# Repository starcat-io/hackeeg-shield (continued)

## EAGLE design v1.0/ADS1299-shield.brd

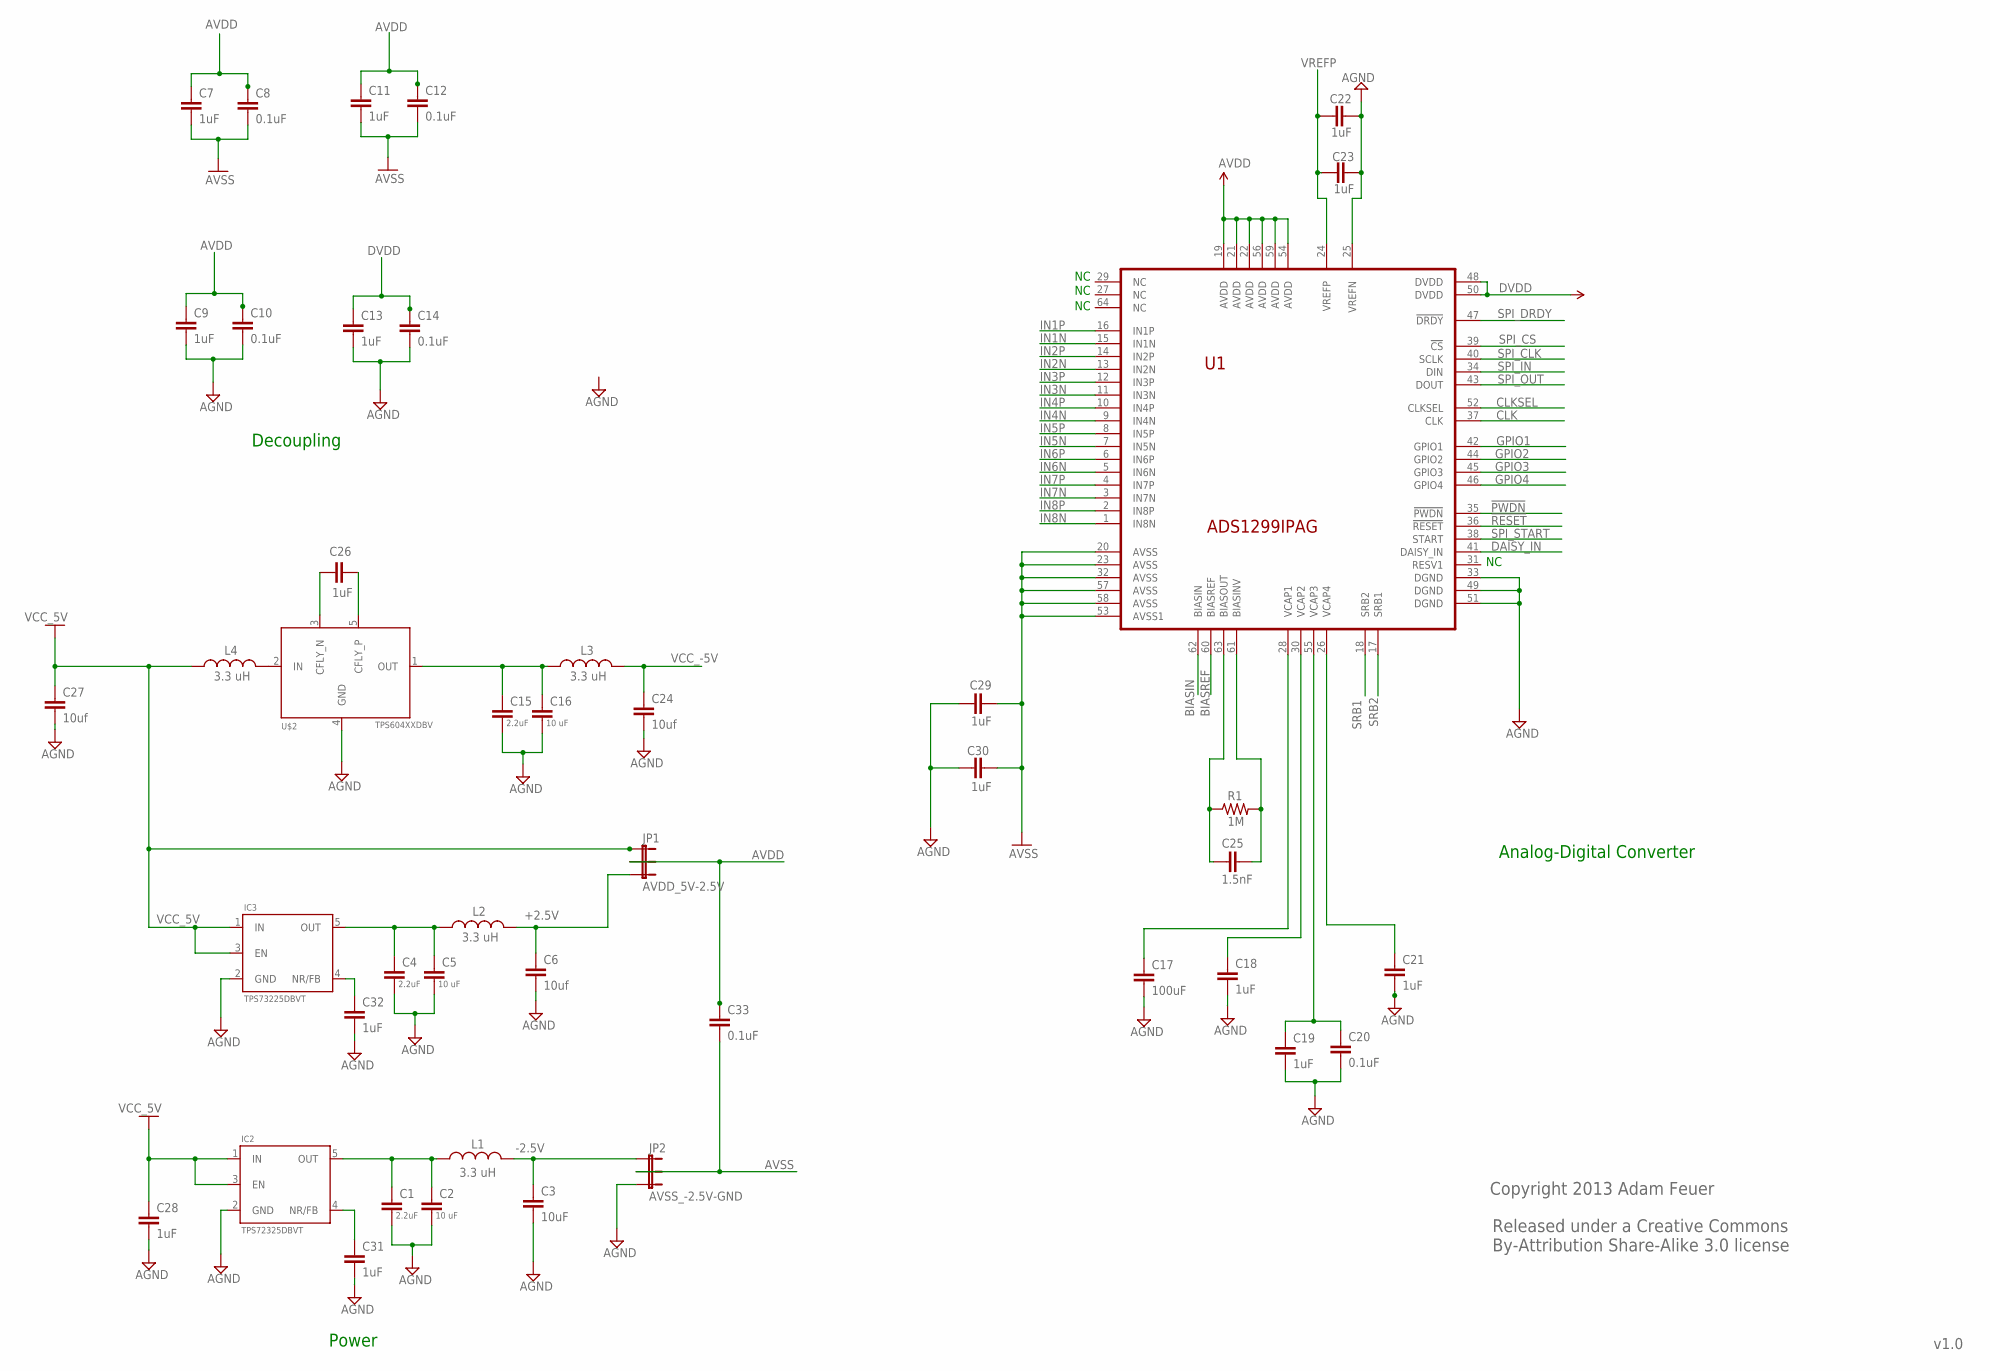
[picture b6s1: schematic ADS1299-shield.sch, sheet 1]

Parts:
C1, C4, C15: 2.2uF; 0603-CAP
C2, C5, C16: 10 uF; 0603-CAP
C3: 10uF; 0603-CAP
C6, C24, C27: 10uf; 0603-CAP
C7, C9, C11, C13, C18, C19, C21, C22, C23, C26, C28, C29, C30, C31, C32: 1uF; 0603-CAP
C8, C10, C12, C14, C20, C33: 0.1uF; 0603-CAP
C17: 100uF; 0603-CAP
C25: 1.5nF; 0603-CAP
IC2: TPS72325DBVT; SOT23-5
IC3: TPS73225DBVT; SOT23-5
JP1: AVDD_5V-2.5V; 1X03
JP2: AVSS_-2.5V-GND; 1X03
L1, L2, L3, L4: 3.3 uH; 0603
R1: 1M; 0603-RES
U1: ADS1299IPAG; TQFP64
U$2: TPS604XXDBV; SOT23-5

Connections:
!PWDN: U1.35 (!PWDN)
!RESET: U1.36 (!RESET)
+2.5V: C6.1, JP1.3, L2.2
-2.5V: C3.1, JP2.1, L1.2
AGND: C1.2, C2.2, C3.2, C4.2, C5.2, C6.2, C9.2, C10.2, C13.2, C14.2, C15.2, C16.2, C17.2, C18.2, C19.2, C20.2, C21.2, C22.2, C23.2, C24.2, C27.2, C28.2, C29.1, C30.1, C31.2, C32.2, IC2.2 (GND), IC3.2 (GND), JP2.3, U1.25 (VREFN), U1.33 (DGND), U1.49 (DGND), U1.51 (DGND), U$2.4 (GND); also elsewhere on the board
AVDD: C7.1, C8.1, C9.1, C10.1, C11.1, C12.1, C33.1, JP1.2, U1.19 (AVDD), U1.21 (AVDD), U1.22 (AVDD), U1.54 (AVDD), U1.56 (AVDD), U1.59 (AVDD)
AVSS: C11.2, C12.2, C29.2, C30.2, C33.2, JP2.2, U1.20 (AVSS), U1.23 (AVSS), U1.32 (AVSS), U1.53 (AVSS1), U1.57 (AVSS), U1.58 (AVSS)
BIASIN: U1.62 (BIASIN)
BIASINV: C25.2, R1.2, U1.61 (BIASINV)
BIASOUT: C25.1, R1.1, U1.63 (BIASOUT)
BIASREF: U1.60 (BIASREF)
CLK: U1.37 (CLK)
CLKSEL: U1.52 (CLKSEL)
DAISY_IN: U1.41 (DAISY_IN)
DVDD: C13.1, C14.1, U1.48 (DVDD), U1.50 (DVDD)
GND: C7.2, C8.2
GPIO1: U1.42 (GPIO1)
GPIO2: U1.44 (GPIO2)
GPIO3: U1.45 (GPIO3)
GPIO4: U1.46 (GPIO4)
IN1N: U1.15 (IN1N); also elsewhere on the board
IN1P: U1.16 (IN1P); also elsewhere on the board
IN2N: U1.13 (IN2N); also elsewhere on the board
IN2P: U1.14 (IN2P)
IN3N: U1.11 (IN3N)
IN3P: U1.12 (IN3P); also elsewhere on the board
IN4N: U1.9 (IN4N); also elsewhere on the board
IN4P: U1.10 (IN4P); also elsewhere on the board
IN5N: U1.7 (IN5N); also elsewhere on the board
IN5P: U1.8 (IN5P); also elsewhere on the board
IN6N: U1.5 (IN6N); also elsewhere on the board
IN6P: U1.6 (IN6P); also elsewhere on the board
IN7N: U1.3 (IN7N); also elsewhere on the board
IN7P: U1.4 (IN7P); also elsewhere on the board
IN8N: U1.1 (IN8N); also elsewhere on the board
IN8P: U1.2 (IN8P); also elsewhere on the board
unnamed: C4.1, C5.1, IC3.5 (OUT), L2.1
unnamed: C1.1, C2.1, IC2.5 (OUT), L1.1
unnamed: C17.1, U1.28 (VCAP1)
unnamed: C18.1, U1.30 (VCAP2)
unnamed: C19.1, C20.1, U1.55 (VCAP3)
unnamed: C15.1, C16.1, L3.1, U$2.1 (OUT)
unnamed: C21.1, U1.26 (VCAP4)
unnamed: C26.2, U$2.5 (CFLY_P)
unnamed: C26.1, U$2.3 (CFLY_N)
unnamed: C32.1, IC3.4 (NR/FB)
unnamed: L4.2, U$2.2 (IN)
unnamed: C31.1, IC2.4 (NR/FB)
SPI_CLK: U1.40 (SCLK)
SPI_CS: U1.39 (!CS)
SPI_DRDY: U1.47 (!DRDY)
SPI_IN: U1.34 (DIN)
SPI_OUT: U1.43 (DOUT)
SPI_START: U1.38 (START)
SRB1: U1.18 (SRB2)
SRB2: U1.17 (SRB1)
VCC_5V: C27.1, IC3.1 (IN), IC3.3 (EN), JP1.1, L4.1
VCC_-5V: C24.1, C28.1, IC2.1 (IN), IC2.3 (EN), L3.2
VREFP: C22.1, C23.1, U1.24 (VREFP)

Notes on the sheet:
Released under a Creative Commons By-Attribution Share-Alike 3.0 license
Copyright 2013 Adam Feuer
v1.0
Decoupling
Power
Analog-Digital Converter

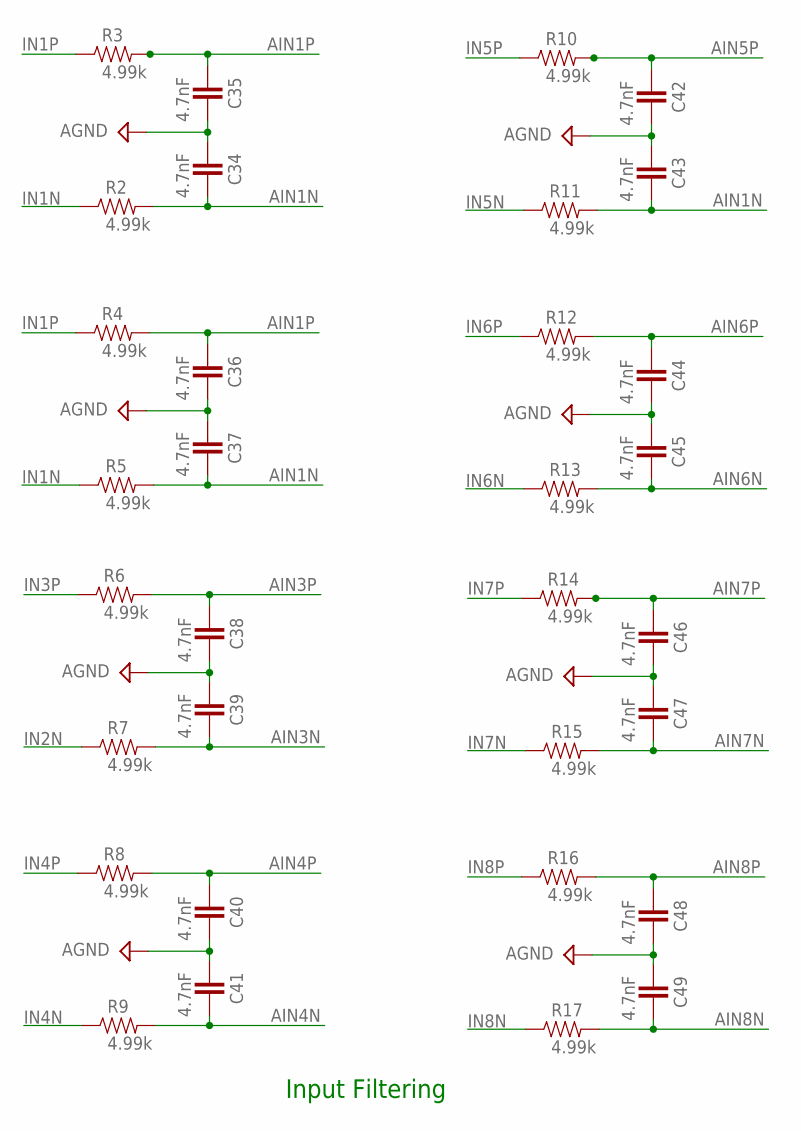
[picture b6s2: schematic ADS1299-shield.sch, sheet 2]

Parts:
C34, C35, C36, C37, C38, C39, C40, C41, C42, C43, C44, C45, C46, C47, C48, C49: 4.7nF; 0603-CAP
R2, R3, R4, R5, R6, R7, R8, R9, R10, R11, R12, R13, R14, R15, R16, R17: 4.99k; 0603-RES

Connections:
AGND: C34.1, C35.2, C36.2, C37.1, C38.2, C39.1, C40.2, C41.1, C42.2, C43.1, C44.2, C45.1, C46.2, C47.1, C48.2, C49.1; also elsewhere on the board
AIN1N: C34.2, C37.2, C43.2, R2.2, R5.2, R11.2
AIN1P: C35.1, C36.1, R3.2, R4.2
AIN3N: C39.2, R7.2
AIN3P: C38.1, R6.2
AIN4N: C41.2, R9.2
AIN4P: C40.1, R8.2
AIN5P: C42.1, R10.2
AIN6N: C45.2, R13.2
AIN6P: C44.1, R12.2
AIN7N: C47.2, R15.2
AIN7P: C46.1, R14.2
AIN8N: C49.2, R17.2
AIN8P: C48.1, R16.2
IN1N: R2.1, R5.1; also elsewhere on the board
IN1P: R3.1, R4.1; also elsewhere on the board
IN2N: R7.1; also elsewhere on the board
IN3P: R6.1; also elsewhere on the board
IN4N: R9.1; also elsewhere on the board
IN4P: R8.1; also elsewhere on the board
IN5N: R11.1; also elsewhere on the board
IN5P: R10.1; also elsewhere on the board
IN6N: R13.1; also elsewhere on the board
IN6P: R12.1; also elsewhere on the board
IN7N: R15.1; also elsewhere on the board
IN7P: R14.1; also elsewhere on the board
IN8N: R17.1; also elsewhere on the board
IN8P: R16.1; also elsewhere on the board

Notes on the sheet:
Input Filtering

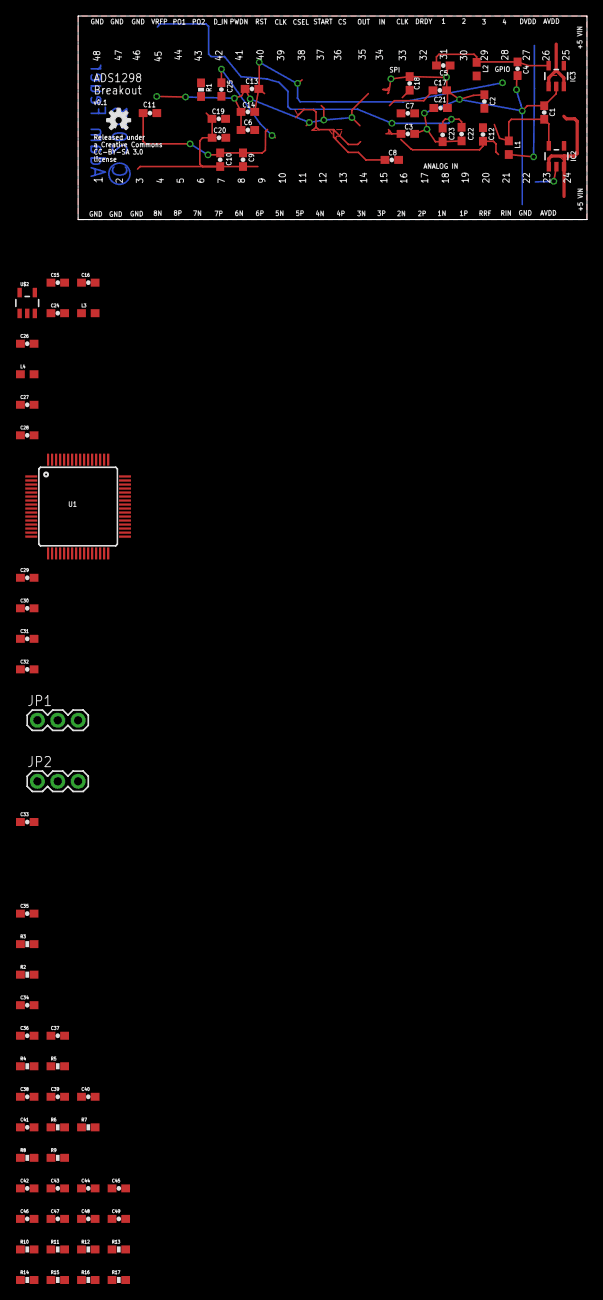
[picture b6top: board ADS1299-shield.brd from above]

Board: 2 copper layers, 63.5 x 25.4 mm, 77 parts (0 on the bottom side), 51 nets.

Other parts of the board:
U$1: OSHW-LOGO-S

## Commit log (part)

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2013-11-05 initial addition, based on ADS1298-breakout
2013-11-06 initial addition of ads129x.lbr - has ADS1298 and ADS1299 chips
2013-11-06 added TI TPS604xx.lbr
2013-11-06 renamed ADS129x.lbr to capitalize ADS
2013-11-06 library-cleanup - positioned symbol corrrectly
2013-11-06 initial addition of OPA376 library
2013-11-06 schematic work - power supplies and decoupling done; updated ADS1299 library symbol to better organize pinouts; minor updates to power supply libraries
2013-11-07 input filtering section done
2013-11-08 configuration jumpers added but not done; EEPROM in and finished; level shifters finished
2013-11-09 configuration jumpers almost complete - board address in, and all configurable digital signals in
2013-11-09 added 2x15 header to header library; used it for electrode connector, which is finished
2013-11-09 removed unneeded burr-brown library
2013-11-10 corrected mixed up N and P pins in OPA375 library; some cleanup
2013-11-11 board outline in, copied from Arduino Due reference design; holes in; connectors in both schematic and board, but not connected in schematic
2013-11-11 all components on board, but not arranged well; connectors not hooked up
2013-11-11 added wires for labeling SPI and XIO connectors
2013-11-11 wires and labels added for SPI and XIO connectors
2013-11-12 all necessary signals routed to shield connectors; schematic passes ERC
2013-11-13 added test points for power; added fiducials; partially grouped AIN block passives, EEPROM resistors, and level shifter decoupling caps
2013-11-13 arranged components by function - AIN filters, ADC and decoupling, power, SRB, Bias, level shifters, EEPROM
2013-11-14 fixed errors in AIN block; some airwires; level shifter output enable is now connected and held high
2013-11-15 changed sync connector to jst 3-pin to support start and clock signals; moved components to place jst connector at board left edge; made ground and power polygons
2013-11-15 new component arrangement - AIN block neat; configuration blocks moved to make more space for routing
2013-11-16 updated 2X10 and 2X12 headers to use smaller pads that can route 2 8mil traces between them; routed SPI MOSI, MISO, and CLK to header pins
2013-11-16 fully routed ADS1299 CLK signal to connector pins
2013-11-17 added autoroute configuration file - this configuration can autoroute the board
2013-11-17 routed I2C signals to EEPROM level shifter - to prevent them from going under the AIN block
2013-11-17 partially routed some signals to avoid autorouter placing signals on DVDD layer - autorouter can route the board only using TOP and BOTTOM layers for signal traces
2013-11-18 routed CLK output around board edge to avoid power supplies
2013-11-19 moved VCC_5V trace from DVDD layer to BOTTOM
2013-11-19 board fully routed - needs cleanup of traces and optimization
2013-11-19 fixed DRC errors related to top-side polygons
2013-11-20 supply polygons for AVDD and AVSS under the ADS1299; more tuning and mitering on top and bottom
2013-11-20 many minor improvements - more mitering polygons, traces enlarged from 6mil to 8mil, clearances improved where possible
2013-11-21 documentation labels done; OSH and CC logos on back of board; increased size of component names for better readability
2013-11-21 fixed problem with test point 2
2013-11-21 added 4-layer ADS1299-shield cam job
2013-11-21 removed unused OSHPark ADS1298 breakout cam job
2013-11-21 updated DRU for tented vias
2013-11-21 updated packaging scripts for ADS1299-shield board
2013-11-23 widened traces; improved jumper clearance for JP5
2013-11-23 initial addition of BOM - has manufacturer, mfg part number, Digikey partnumber and url, SMT/Through-hole, pins, size, notes
2013-11-23 updated stats and costs sheets
2013-11-23 added endless knot logo to back of board
2013-11-25 updated BOM with new and changed parts - needs to be checked once more
2013-11-25 minor updates to some component positioning
2013-11-25 updated cam job to not output tDocu; fixed problems with some top polygons
2013-11-25 added advanced circuits packager; updated other packagers to remove temp packaging dir before packaging
2013-12-28 fixes to schematic and board - created VCC_5V_FILTERED net to correct current draw problem; changed inductors to 0805 to fix current flow problem
2013-12-28 updated packaging script to help AC recognize files better
2013-12-29 adding autoroute settings
2013-12-29 made lable text bigger and repositioned; added Arduino pin labels; added 1uf cap to 2.5 power supple to match eval board; relabeled power and buffer 3-pin jumpers with numbers instead of letters, to 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
2013-12-29 minor trace clearance change
2013-12-29 minor updates to trace clearances; moved logos on bottom of board so the don't cover the copyright
2013-12-31 changed serial EEPROM to use I2C port SDA/SCL instead of SDA1/SCL1 due to lack of pull up resistors and Mega2560 incompatibility (Mega2560 has pull-ups on those pins already; Due doesn't)
2014-01-01 renamed TPS32xx library to TPS732xx; fixed incorrect pin mapping
2014-01-02 renamed shield files to hackeeg
2014-01-03 widening AVSS trace widths
2014-01-07 minor text positioning improvements
2014-01-07 renamed cam and bom files to hackeeg
2014-01-07 updated packaging scripts for hackeeg
2014-01-07 switched red and white LEDs - red is now power
2014-01-09 minor changes to silkscreen
2014-01-09 updated BOM to used JST through-hole connector for sync; fixed bottomlayer trace widths and routing
2014-01-09 updated board revision to 1.1.1; update package-seeed script
2014-01-16 fixed some BOM URLs and part numbers after rev 1.1 Digikey/Mouser order
2014-01-16 fixed silkscreen pin label bug - DAC0/1, CAN RX/TX
2014-01-22 no changes to bom, playing with manufacturing estimator
2014-01-22 minor changes to BIASINV solder pad
2014-01-22 layout cleanup
2014-01-22 changing print area
2014-01-25 changed solder mask (cream) stop to 1mil so stencils cut correctly using gerber2graphtec & graphtec cameo cutter
2014-01-26 BOM updates fixing place sheet after building rev 1.1 - to match BOM sheet
2014-01-26 added circular restrict polygons on AGND and DVDD layers, surrounding mounting holes - to avoid problems with Advanced Circuits plating the holes and causing short circuits
2014-01-27 updated IC10,11 names and package TSSOP20 on place sheet
2014-01-27 changed TXS0102DCTR to TXS0102DCUR on place sheet
2014-01-28 changed inner layer (AGND and DVDD) polygon isolate clearance to 12 mils (from 0)
2014-01-28 changed rest-rings to min 12mil and fixed all DRC errors
2014-01-29 updated layer AGND and DVDD text to have larger widths and enclosing cutout box to prevent clearance errors
2014-01-29 updated board version number to 1.2.4
2014-02-04 fixed problem with jumper legend lines being on bottom of board - moved to top
2014-02-07 improving trace clearances
2014-02-13 updated some business planning calculations
2014-02-16 improved AVSS trace width on bottom layer; removed trace running through the middle of caps; improved text sizes for configuration labels
2014-02-16 improved trace routing on bottom layer
2014-02-17 added AVSS polygon to bottom layer to join disconnected AVSS segments; widened a lot of AVDD and AVSS traces
2014-02-17 changed copper text spacing on Layer 4 (bottom) to fix hole-text clearance
2014-09-13 updated README file for ADS1299
2014-09-13 added hackeeg cam files for v1.3.1
2014-09-14 rotating schematic pages to be horizontal
2014-09-14 updating license to cc-by-sa-4.0 international
2014-09-14 moved endless-knot.lbr to eagle dir
2014-09-14 added picture to README
2014-12-03 moved schematic PDF to main directory
2014-12-03 moved board photo to main directory
2014-12-05 updated pdf
2016-06-05 initial addition of connector and jumper pinouts
2016-06-05 change email and website
2016-06-05 change website to https
2016-06-05 signature formatting
2016-06-05 moved BOARD LED to Not Configurable section
2016-06-06 fix for bipolar mode 2.25x problem (VREFN-AVSS)
    - disconnected VREFN from AGND
    - connected VREFN to AVSS
    - rerouted traces
    - minor labeling changes - labeled all board to board connectors
    - bumped version to 1.4.0
2016-07-22 changed C22 to 10uF; C23 to 0.1uF
    - to match eval board schematic
    - and added VREFP test point
2016-07-22 increased LED ground trace width
2016-08-29 updated schematic PDF
2016-09-01 fixing schematic PDF
2016-09-22 minor routing adjustments
    - for JP9 clearance
2018-08-06 save in Eagle 9.1
2018-08-26 variants for various sizes of holes
    - for testing fit
    - 100%, 105%, 110%, 115%, 120%
2018-09-03 packaging improvements
2018-09-03 switch dimensions to inches; add simple connector footprint variants
2018-09-07 named schematic sheets
2018-09-07 initial addition of sullins 24 pos smt header lbr
2018-09-07 initial addition of connector test sch and brd
2018-09-09 made board smaller; trace width increased to 12mil
    - from 8mil
2018-09-10 initial addition of 24 and 32 connector boards
2018-09-24 removed ground planes
    - to reduce noise
2018-09-24 added connector-test.pro
2018-09-24 removed all po-37729 variants
    - since hex110 (110%) is working fine
2018-09-25 Revert "removed ground planes"
    This reverts commit f4ca484e04cfc3e6669577150c464fbf194e8d2b.
2018-09-25 connected IN1-8N to ground
    - for cable noise reduction
2018-09-25 updated libraries to current
2018-12-01 connector-8 as sent to macrofab initial run
2018-12-01 added two additional mounting holes
    - to prevent bending problems.
2019-04-16 corrected connector spacing and made board smaller
    - all connectors are now evenly spaced
2019-04-18 made mounting holes 3.3mm to fit m3 screws
2019-04-19 initial addition of wire-connector-12 board
    - will be screw terminal board
2019-04-23 added connector, finished schematic and routed
2019-04-24 put wire connector on bottom of board
    - labeled wire connector pins
    - board is routed
2019-04-24 moved wire connector legend to top
2019-04-24 added OSTTA120161.lbr
2019-04-24 replaced OSTTA120161B with OSTTA120161 library
2019-05-01 added On Shore 302-S241 vert header library
2019-05-02 minor routing updates to electrode input
2019-05-02 moved fiducials out from under connectors
2019-05-07 updated HackEEG version number on PCB to 1.4.2 GA
2019-05-07 bump schematic version to 1.4.2 to match PCB
2019-05-07 updated readme with CrowdSupply info
2019-05-07 updated HackEEG picture
2019-05-07 bolded warning text
    - instead of italics
2019-05-07 updated first paragraph with TI ADS1299 app info
2019-05-09 formatting changes - using tables in connectors.md
2019-05-10 converted configuration to use markdown tables
2019-05-10 added SRB and BIAS jumper configuration info
2019-05-11 update docs with hyperlinks
    - also add packaging script
    - set layer visibility
2019-05-11 fix bad link - wrong location
2019-05-13 removed Starcat wifi shield from docs
    - since it won't be produced
2019-05-13 fixed JP3 label (was mistakenly labeled JP0)
    - also formatting changes
2019-05-13 added single-ended clarification
2019-05-14 formatting improvements
2019-05-24 changed page orientation on schematic pdf
    - so the pages are rotated correctly
2019-06-04 minor safety wording update
2019-06-04 minor board legend updates
2019-06-24 restore old version of po-37729.lbr for single-hole variants
2019-06-24 initial addition of po-41829 horizontal DIN 42-802 connector
    - wave solderable
2019-06-24 relicense to CERN OHL 1.2 - LICENSE and README files
2019-06-24 relicense to CERN OHL 1.2 - hackeeg-shield sch and brd
2019-06-24 relicense to CERN OHL 1.2 - sch
2019-06-24 removed creative-commons.lbr - not necessary with CERN OHL
2019-12-13 update readme for crowsupply campaign
2019-12-14 fixed support language in readme
2020-01-29 fix readme links
2020-01-29 fixed missing word (repo)
2020-02-14 add 2-pin JST connector for REF_ELEC multiboard
2020-02-14 update copper copyright notice
2020-09-18 reference electrode connection for multiboard
